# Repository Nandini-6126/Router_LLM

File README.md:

An intelligent PCB design tool that leverages Gemini 2.0 Flash to analyze KiCad electrical nets and generate optimized routing rules. It features a FastAPI backend for complex A* routing logic and a React-based dashboard for real-time visualization and statistics.

Features
AI-Driven Net Analysis: Automatically classifies nets (Power, Data, Sensitive) to suggest optimal trace widths and clearances.

Advanced A Router*: High-efficiency pathfinding that accounts for pad density and global design constraints.

Manual Overrides: Hybrid mode allowing users to specify expert rules that bypass AI suggestions.

Real-time Dashboard: Live tracking of routing efficiency, successful connections, and failed net statistics.

Tech Stack
Backend: Python 3.10+, FastAPI, Uvicorn.

Frontend: React.js, Tailwind CSS, Axios.

AI Integration: Google Gemini 2.0 Flash API.

PCB Processing: KiCad file parsing and merging logic.

Getting Started for Testing
Prerequisites
Python 3.9+ and Node.js/npm must be installed.

A Google AI Studio API Key is required for the AI Advisor.

1. Environment Configuration
To keep the API key secure, set it as an environment variable in your terminal.

Windows (PowerShell): $env:GEMINI_API_KEY="your_api_key_here"

Mac/Linux: export GEMINI_API_KEY="your_api_key_here"

2. Backend Setup
Navigate to the backend directory: cd backend.

Create and activate a virtual environment:

Windows: python -m venv venv followed by .\venv\Scripts\activate

Mac/Linux: python3 -m venv venv followed by source venv/bin/activate

Install dependencies: pip install fastapi uvicorn requests python-multipart.

Start the server: python -m uvicorn router_server:app --reload.

3. Frontend Setup
Open a new terminal and navigate to the frontend: cd frontend.

Install Node packages: npm install.

Launch the application: npm start.

Access the UI at http://localhost:3000.

📍 How to Run a Test
Prepare File: Have a .kicad_pcb file ready for upload.

Set Rules: Use the "Design Rules" card in the UI to enter optional manual constraints (Clearance, Trace Width).

Run AI Advisor: Click "Run Auto-Router." The backend will first call the Gemini API to analyze your nets.

Review Stats: Once finished, check the dashboard for Routing Efficiency and Total Connections.

Download: The routed board will automatically download as a .zip containing the new .kicad_pcb and routing CSV.

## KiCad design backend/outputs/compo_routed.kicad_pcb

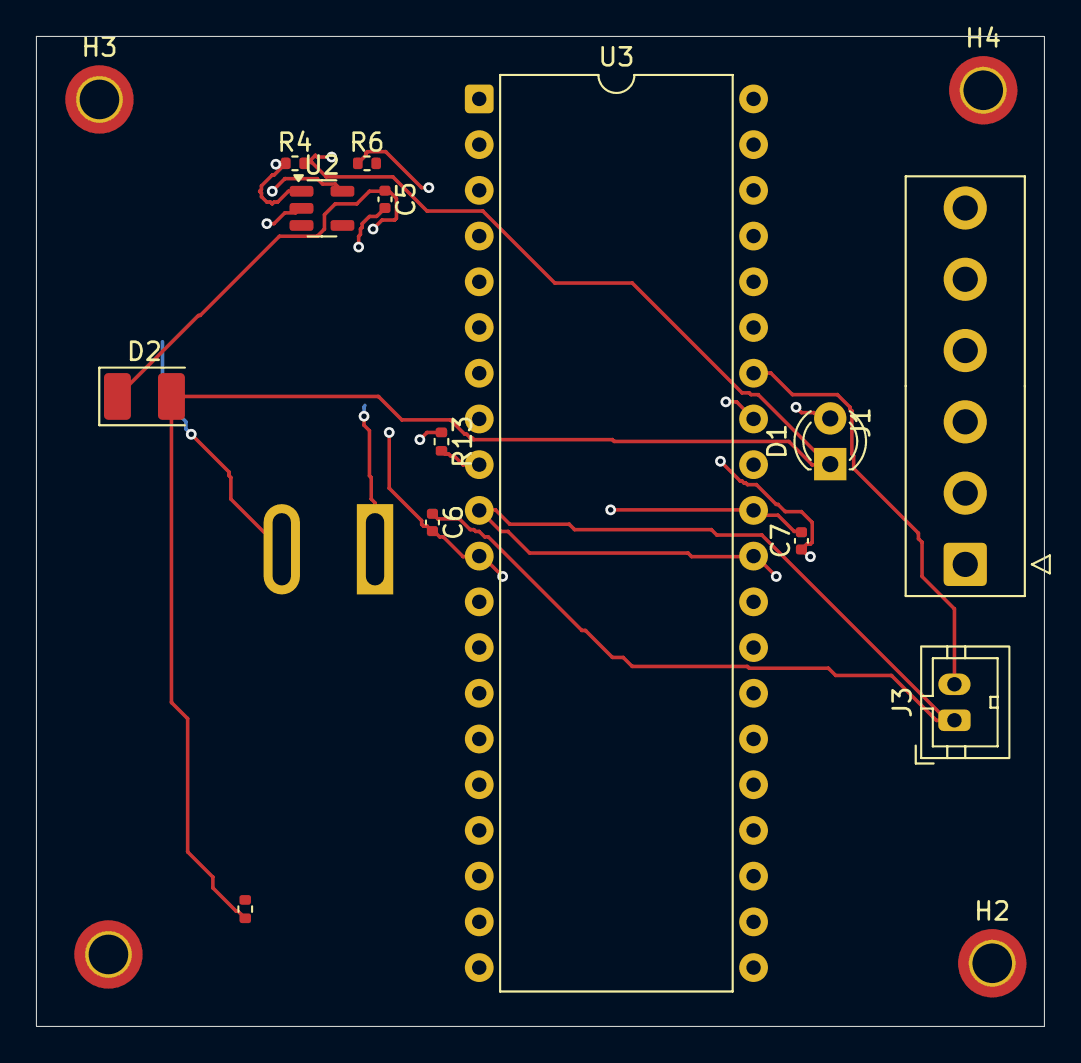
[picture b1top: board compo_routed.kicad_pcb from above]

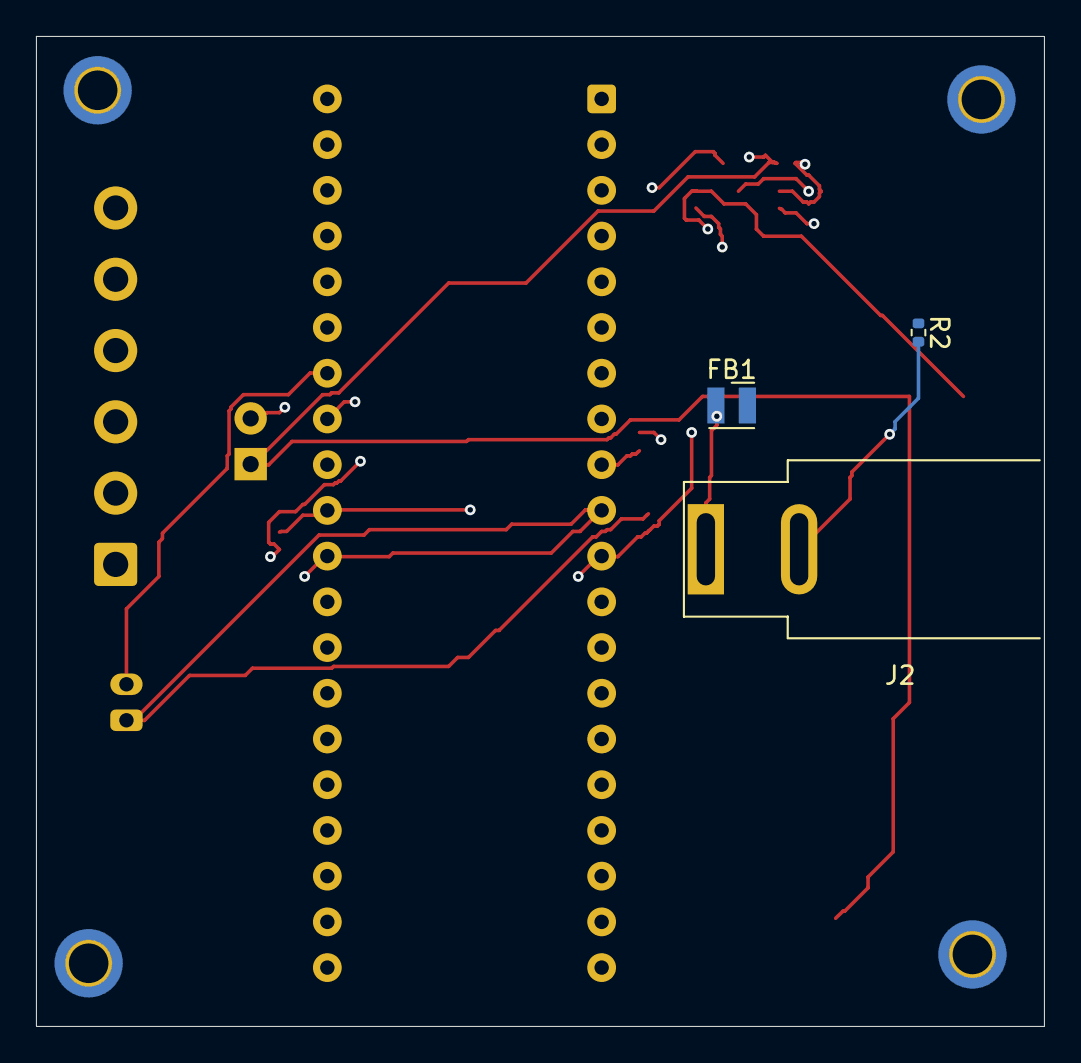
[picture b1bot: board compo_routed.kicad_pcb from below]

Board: 4 copper layers, 56.0 x 55.0 mm, 20 parts (3 on the bottom side), 7 nets.

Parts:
C5, C6, C7: C; C_0402_1005Metric
D1: LED; LED_D3.0mm
D2: LED; LED_PLCC-2_3.4x3.0mm_AK
FB1: FerriteBead; L_Wurth_WE-LQSH-2512
H1, H2, H3, H4: MountingHole; MountingHole_2.2mm_M2_DIN965_Pad_TopBottom
J1: Conn_01x06_Pin; TE_826576-6_1x06_P3.96mm_Vertical
J2: Barrel_Jack; BarrelJack_SwitchcraftConxall_RAPC10U_Horizontal
J3: Conn_01x02_Pin; TE_440054-2_1x02_P2.00mm_Vertical
R2, R4, R6, R13, R15: R; R_0402_1005Metric
U2: MIC5504-1.2YM5; SOT-23-5
U3: ATmega164P-20P; DIP-40_W15.24mm

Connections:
+1V2: C5.1, C6.1, C7.1, D2.2 (A), J3.1, R6.1, U2.5 (VOUT), U3.10 (VCC), U3.30 (AVCC)
+3V3: R4.1, R13.1, U2.1 (VIN)
GND: C5.2, C6.2, C7.2, D1.1 (K), D2.1 (K), J2.2, R2.2, R4.2, R6.2, R15.2, U2.2 (GND), U3.11 (GND), U3.31 (GND)
unnamed: D1.2 (A), U3.33 (PA7)
unnamed: FB1.1, J2.1
unnamed: J3.2, U3.34 (PA6)
unnamed: R13.2, U3.9 (~RESET)

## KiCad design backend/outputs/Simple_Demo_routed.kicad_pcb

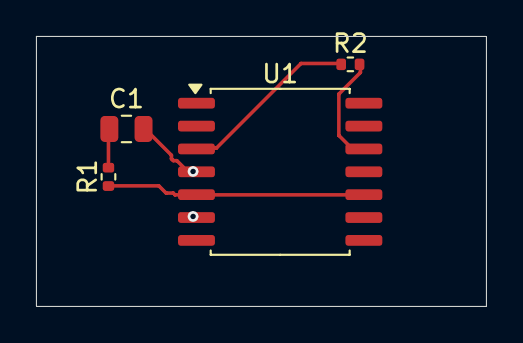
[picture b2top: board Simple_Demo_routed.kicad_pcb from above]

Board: 4 copper layers, 25.0 x 15.0 mm, 4 parts (0 on the bottom side), 5 nets.

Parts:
C1: C; C_0805_2012Metric
R1, R2: R; R_0402_1005Metric
U1: LM2574HVM-3.3; SOIC-14W_7.5x9mm_P1.27mm

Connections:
GND: C1.2, U1.4 (SGND), U1.6 (PGND)
unnamed: C1.1, R1.2
unnamed: R2.1, U1.3 (FB)
unnamed: R2.2, U1.12 (OUT)
VCC: R1.1, U1.5 (~ON/OFF), U1.10 (VIN)

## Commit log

2025-12-10 Initial commit: AI PCB Router, LLM Implemented
2025-12-18 Integrated Gemini 2.0 and added routing dashboard
2025-12-18 Initialize README with project overview and setup
    Added detailed project description, features, tech stack, and setup instructions.
2025-12-18 Added SQLite history tracking and expanded design rule UI
2025-12-18 Refactor: Improve UI and add zoom functionality to PCBViewer
2025-12-27 feat: Add direct download and improve output generation
    This commit introduces a new endpoint for direct ZIP file downloads,
    improving performance by avoiding base64 encoding. It also refactors
    the output generation to work in-memory, further optimizing the process.
    The frontend is updated to prefer the new download URL and handle
    both new and old response formats.
